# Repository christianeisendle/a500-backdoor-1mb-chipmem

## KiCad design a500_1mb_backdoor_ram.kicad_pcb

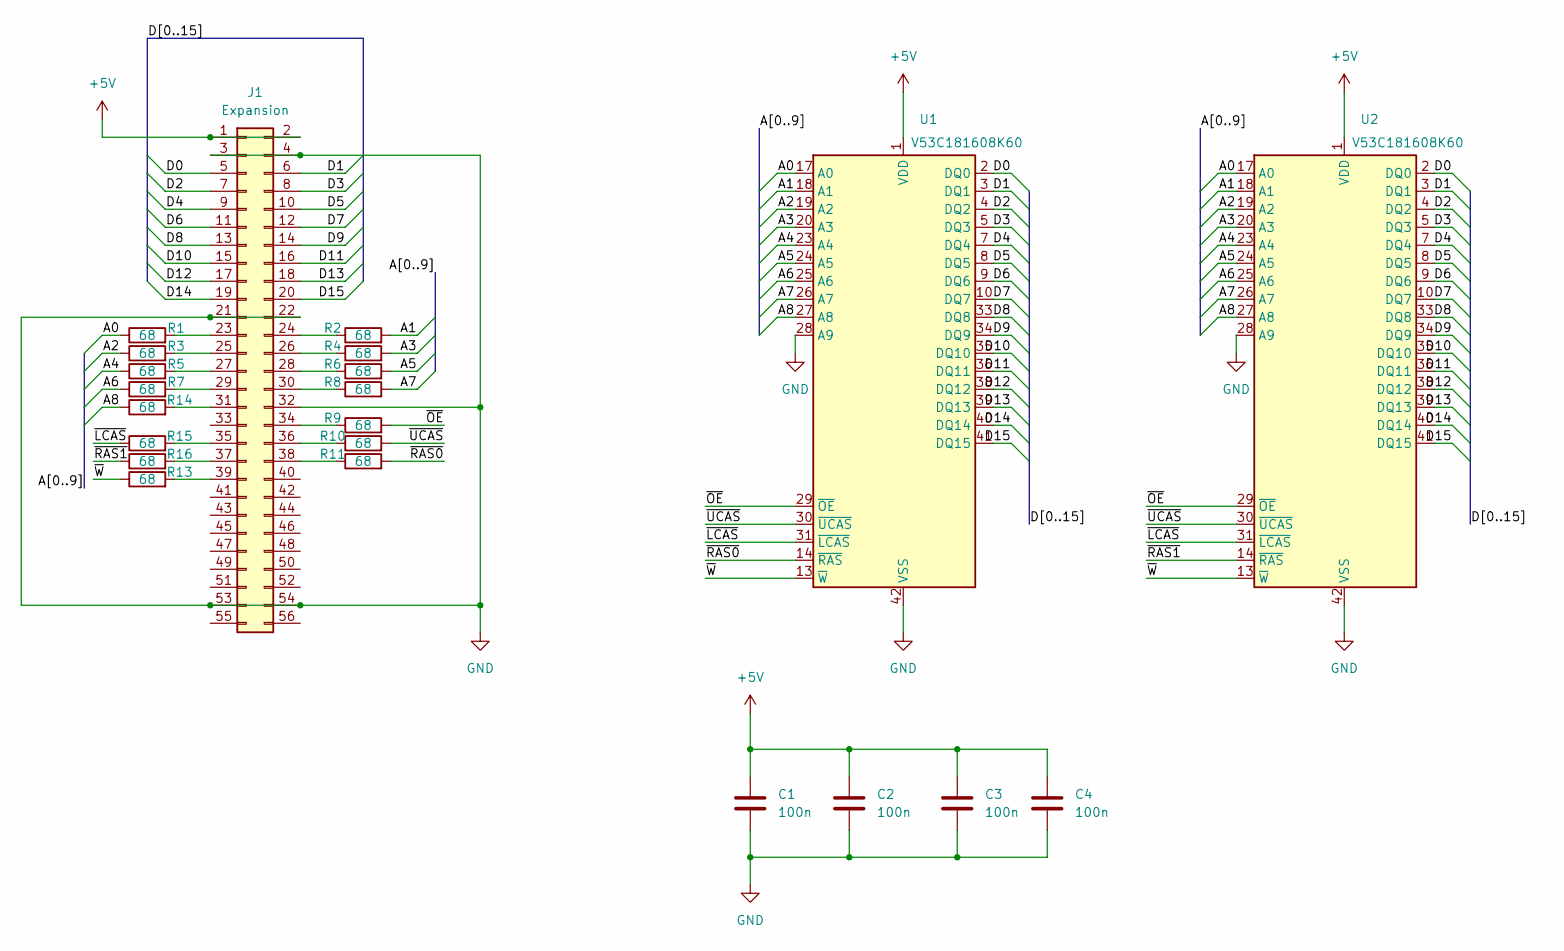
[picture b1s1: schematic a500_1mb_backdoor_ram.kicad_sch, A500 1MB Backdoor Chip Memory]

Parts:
C1, C2, C3, C4: 100n; C_0402_1005Metric
J1: Expansion; PinSocket_2x28_P2.54mm_Horizontal
R1, R2, R3, R4, R5, R6, R7, R8, R9, R10, R11, R13, R14, R15, R16: 68; R_0402_1005Metric
U1, U2: V53C181608K60; SOJ-42_10.16x27.46mm_P1.27mm

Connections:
+5V: C1.1, C2.1, C3.1, C4.1, J1.1, J1.2, U1.1 (VDD), U1.6 (VDD), U1.21 (VDD), U2.1 (VDD), U2.6 (VDD), U2.21 (VDD)
/A0: R1.1, U1.17 (A0), U2.17 (A0)
/A1: R2.2, U1.18 (A1), U2.18 (A1)
/A2: R3.1, U1.19 (A2), U2.19 (A2)
/A3: R4.2, U1.20 (A3), U2.20 (A3)
/A4: R5.1, U1.23 (A4), U2.23 (A4)
/A5: R6.2, U1.24 (A5), U2.24 (A5)
/A6: R7.1, U1.25 (A6), U2.25 (A6)
/A7: R8.2, U1.26 (A7), U2.26 (A7)
/A8: R14.1, U1.27 (A8), U2.27 (A8)
/D0: J1.5, U1.2 (DQ0), U2.2 (DQ0)
/D1: J1.6, U1.3 (DQ1), U2.3 (DQ1)
/D2: J1.7, U1.4 (DQ2), U2.4 (DQ2)
/D3: J1.8, U1.5 (DQ3), U2.5 (DQ3)
/D4: J1.9, U1.7 (DQ4), U2.7 (DQ4)
/D5: J1.10, U1.8 (DQ5), U2.8 (DQ5)
/D6: J1.11, U1.9 (DQ6), U2.9 (DQ6)
/D7: J1.12, U1.10 (DQ7), U2.10 (DQ7)
/D8: J1.13, U1.33 (DQ8), U2.33 (DQ8)
/D9: J1.14, U1.34 (DQ9), U2.34 (DQ9)
/D10: J1.15, U1.35 (DQ10), U2.35 (DQ10)
/D11: J1.16, U1.36 (DQ11), U2.36 (DQ11)
/D12: J1.17, U1.38 (DQ12), U2.38 (DQ12)
/D13: J1.18, U1.39 (DQ13), U2.39 (DQ13)
/D14: J1.19, U1.40 (DQ14), U2.40 (DQ14)
/D15: J1.20, U1.41 (DQ15), U2.41 (DQ15)
/~LCAS: R15.1, U1.31 (~LCAS), U2.31 (~LCAS)
/~OE: R9.2, U1.29 (~OE), U2.29 (~OE)
/~RAS0: R11.2, U1.14 (~RAS)
/~RAS1: R16.1, U2.14 (~RAS)
/~UCAS: R10.2, U1.30 (~UCAS), U2.30 (~UCAS)
/~W: R13.1, U1.13 (~W), U2.13 (~W)
GND: C1.2, C2.2, C3.2, C4.2, J1.3, J1.4, J1.21, J1.22, J1.32, J1.53, J1.54, U1.22 (VSS), U1.28 (A9), U1.37 (VSS), U1.42 (VSS), U2.22 (VSS), U2.28 (A9), U2.37 (VSS), U2.42 (VSS)
unnamed: J1.23, R1.2
unnamed: J1.24, R2.1
unnamed: J1.25, R3.2
unnamed: J1.26, R4.1
unnamed: J1.27, R5.2
unnamed: J1.28, R6.1
unnamed: J1.29, R7.2
unnamed: J1.30, R8.1
unnamed: J1.31, R14.2
unnamed: J1.34, R9.1
unnamed: J1.35, R15.2
unnamed: J1.36, R10.1
unnamed: J1.37, R16.2
unnamed: J1.38, R11.1
unnamed: J1.39, R13.2

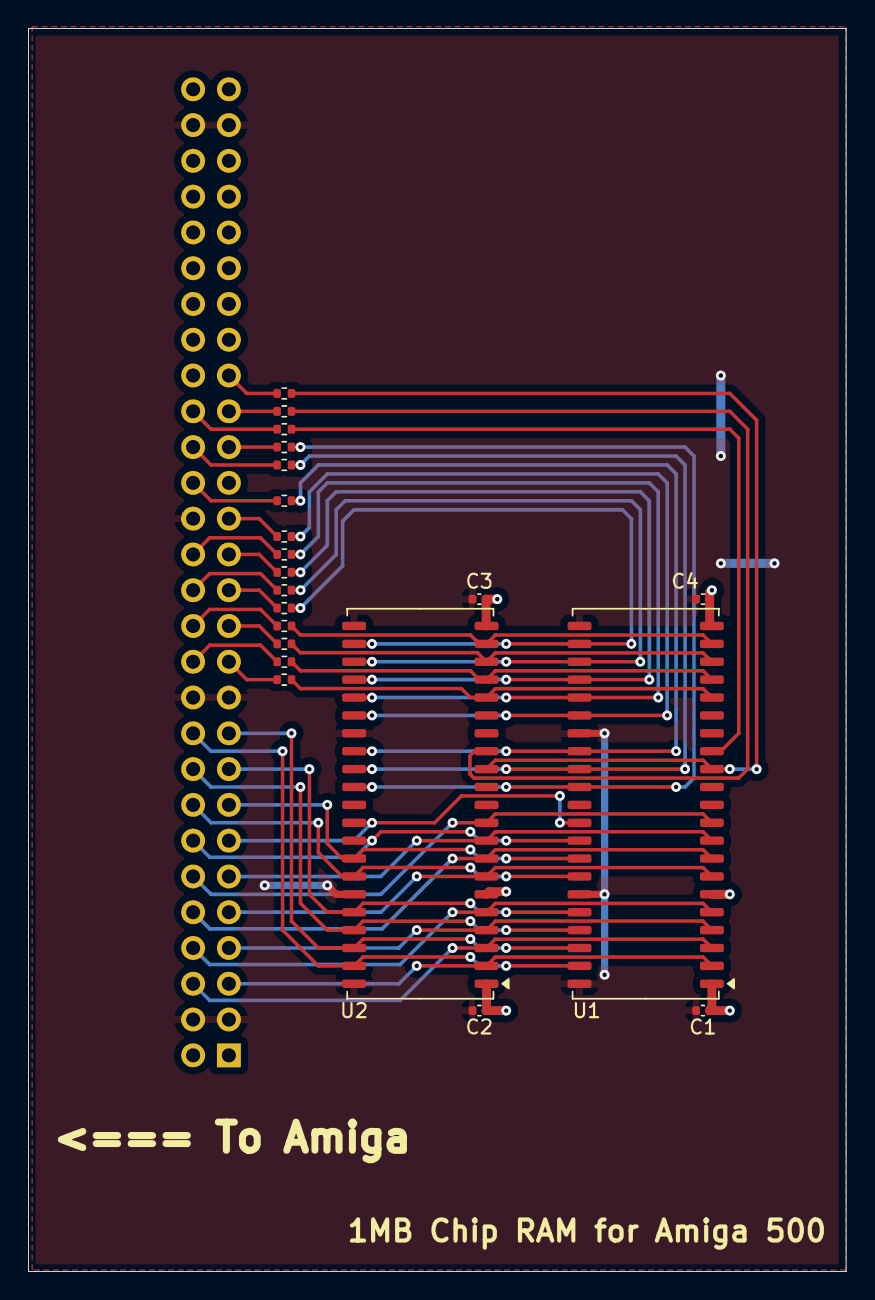
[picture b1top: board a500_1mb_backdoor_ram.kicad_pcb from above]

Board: 2 copper layers, 58.0 x 88.2 mm, 22 parts (1 on the bottom side), 48 nets.

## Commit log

2025-01-12 Initial commit v1.0
2025-02-02 Version 2.0 - fixing GND vs. VDD connection
